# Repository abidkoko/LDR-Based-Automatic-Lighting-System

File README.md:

# LDR-Based-Automatic-Lighting-System
Sistem lampu otomatis berbasis sensor LDR yang mampu menyesuaikan pencahayaan sesuai kondisi lingkungan.

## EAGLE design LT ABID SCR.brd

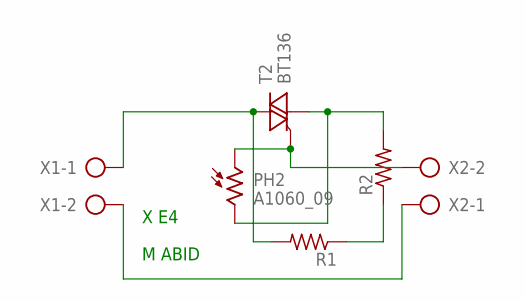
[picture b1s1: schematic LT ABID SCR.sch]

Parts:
PH2: A1060_09; T0-46-A10XX
R1, R2: R-US_0204/7; 0204/7
T2: BT136; TO220AB
X1, X2: AK300/2

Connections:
unnamed: PH2.2, R2.2, T2.1 (A1)
unnamed: R1.1, R2.1
unnamed: PH2.1, T2.3 (G), X2.2
unnamed: R1.2, T2.2 (A2), X1.1
unnamed: X1.2, X2.1

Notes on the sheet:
M ABID
X E4

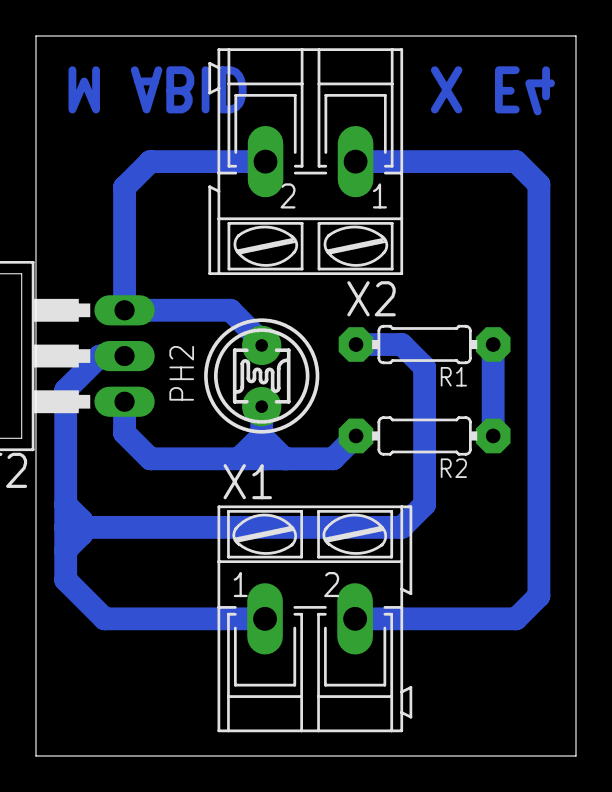
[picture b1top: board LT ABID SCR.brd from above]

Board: 2 copper layers, 30.0 x 40.0 mm, 6 parts (0 on the bottom side), 5 nets.
